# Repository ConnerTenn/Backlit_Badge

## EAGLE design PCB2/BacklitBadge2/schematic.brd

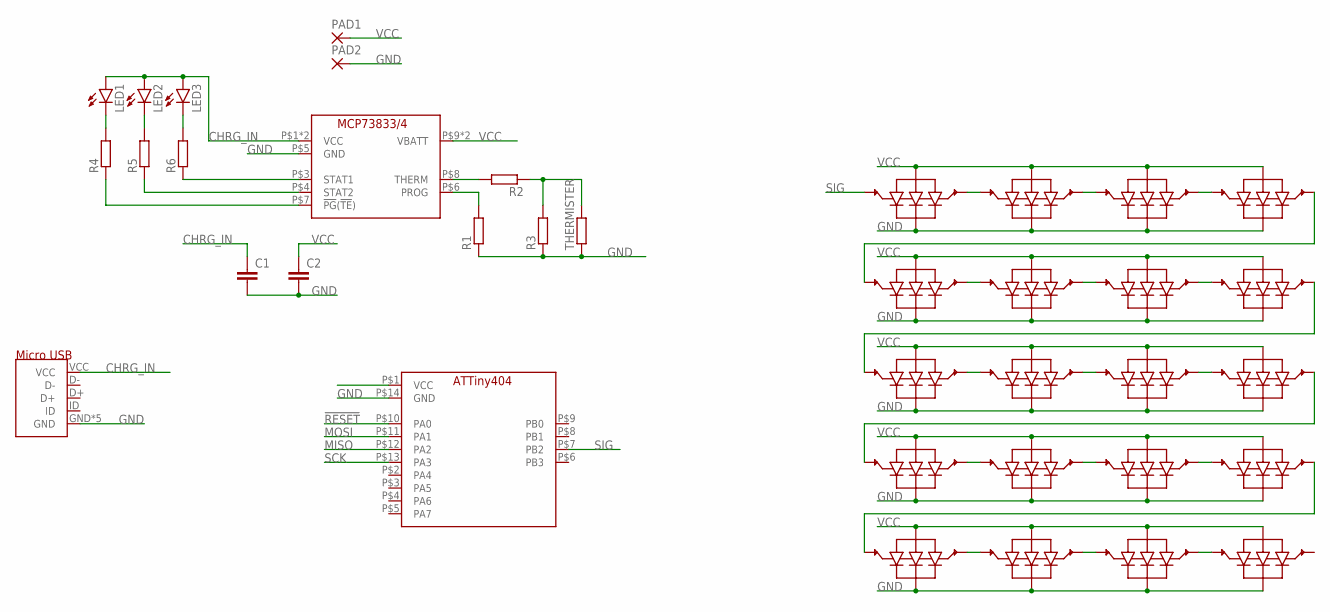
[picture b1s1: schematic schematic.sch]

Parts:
C1, C2: CC1206; C1206
LED1, LED2, LED3: LEDSML1206; SML1206
PAD1, PAD2: 1,6/0,8
R1, R2, R3, R4, R5, R6: RR1206; R1206
THERMISTER: RR1206; R1206
U$1: ATTINY404; 14-SOIC
U$2: MCP73833/4; 10-MSOP
U$3, U$4, U$5, U$6, U$7, U$8, U$9, U$10, U$11, U$12, U$13, U$14, U$15, U$16, U$17, U$18, U$19, U$20, U$21, U$22: WS2812B; 5050-THRU
U$23: MICROUSB

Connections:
!RESET: U$1.P$10 (PA0)
CHRG_IN: C1.1, LED1.A, LED2.A, LED3.A, U$2.P$1 (VCC), U$2.P$2 (VCC), U$23.VCC
GND: C1.2, C2.2, PAD2.1, R1.1, R3.1, THERMISTER.1, U$1.P$14 (GND), U$2.P$5 (GND), U$3.P$3 (GND), U$4.P$3 (GND), U$5.P$3 (GND), U$6.P$3 (GND), U$7.P$3 (GND), U$8.P$3 (GND), U$9.P$3 (GND), U$10.P$3 (GND), U$11.P$3 (GND), U$12.P$3 (GND), U$13.P$3 (GND), U$14.P$3 (GND), U$15.P$3 (GND), U$16.P$3 (GND), U$17.P$3 (GND), U$18.P$3 (GND), U$19.P$3 (GND), U$20.P$3 (GND), U$21.P$3 (GND), U$22.P$3 (GND), U$23.GND, U$23.GND2 (GND), U$23.GND3 (GND), U$23.GND4 (GND), U$23.GND5 (GND)
MISO: U$1.P$12 (PA2)
MOSI: U$1.P$11 (PA1)
unnamed: U$3.P$2 (DOUT), U$4.P$4 (DIN)
unnamed: U$7.P$2 (DOUT), U$8.P$4 (DIN)
unnamed: R1.2, U$2.P$6 (PROG)
unnamed: R2.2, U$2.P$8 (THERM)
unnamed: R2.1, R3.2, THERMISTER.2
unnamed: LED1.C, R4.2
unnamed: LED2.C, R5.2
unnamed: R6.1, U$2.P$3 (STAT1)
unnamed: LED3.C, R6.2
unnamed: U$13.P$2 (DOUT), U$19.P$4 (DIN)
unnamed: U$5.P$2 (DOUT), U$6.P$4 (DIN)
unnamed: U$9.P$2 (DOUT), U$14.P$4 (DIN)
unnamed: U$17.P$2 (DOUT), U$18.P$4 (DIN)
unnamed: R5.1, U$2.P$4 (STAT2)
unnamed: U$10.P$2 (DOUT), U$11.P$4 (DIN)
unnamed: U$11.P$2 (DOUT), U$12.P$4 (DIN)
unnamed: U$12.P$2 (DOUT), U$13.P$4 (DIN)
unnamed: U$4.P$2 (DOUT), U$5.P$4 (DIN)
unnamed: U$8.P$2 (DOUT), U$9.P$4 (DIN)
unnamed: U$16.P$2 (DOUT), U$17.P$4 (DIN)
unnamed: U$21.P$2 (DOUT), U$22.P$4 (DIN)
unnamed: U$20.P$2 (DOUT), U$21.P$4 (DIN)
unnamed: U$15.P$2 (DOUT), U$16.P$4 (DIN)
unnamed: U$18.P$2 (DOUT), U$20.P$4 (DIN)
unnamed: U$14.P$2 (DOUT), U$15.P$4 (DIN)
unnamed: U$6.P$2 (DOUT), U$7.P$4 (DIN)
unnamed: U$3.P$4 (DIN), U$19.P$2 (DOUT)
unnamed: R4.1, U$2.P$7 (!PG!(!TE!))
SCK: U$1.P$13 (PA3)
SIG: U$1.P$7 (PB2), U$10.P$4 (DIN)
VCC: C2.1, PAD1.1, U$2.P$9 (VBATT), U$2.P$10 (VBATT), U$3.P$1 (VCC), U$4.P$1 (VCC), U$5.P$1 (VCC), U$6.P$1 (VCC), U$7.P$1 (VCC), U$8.P$1 (VCC), U$9.P$1 (VCC), U$10.P$1 (VCC), U$11.P$1 (VCC), U$12.P$1 (VCC), U$13.P$1 (VCC), U$14.P$1 (VCC), U$15.P$1 (VCC), U$16.P$1 (VCC), U$17.P$1 (VCC), U$18.P$1 (VCC), U$19.P$1 (VCC), U$20.P$1 (VCC), U$21.P$1 (VCC), U$22.P$1 (VCC)

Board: 2 copper layers, 37 parts (20 on the bottom side), 32 nets, no tracks yet.

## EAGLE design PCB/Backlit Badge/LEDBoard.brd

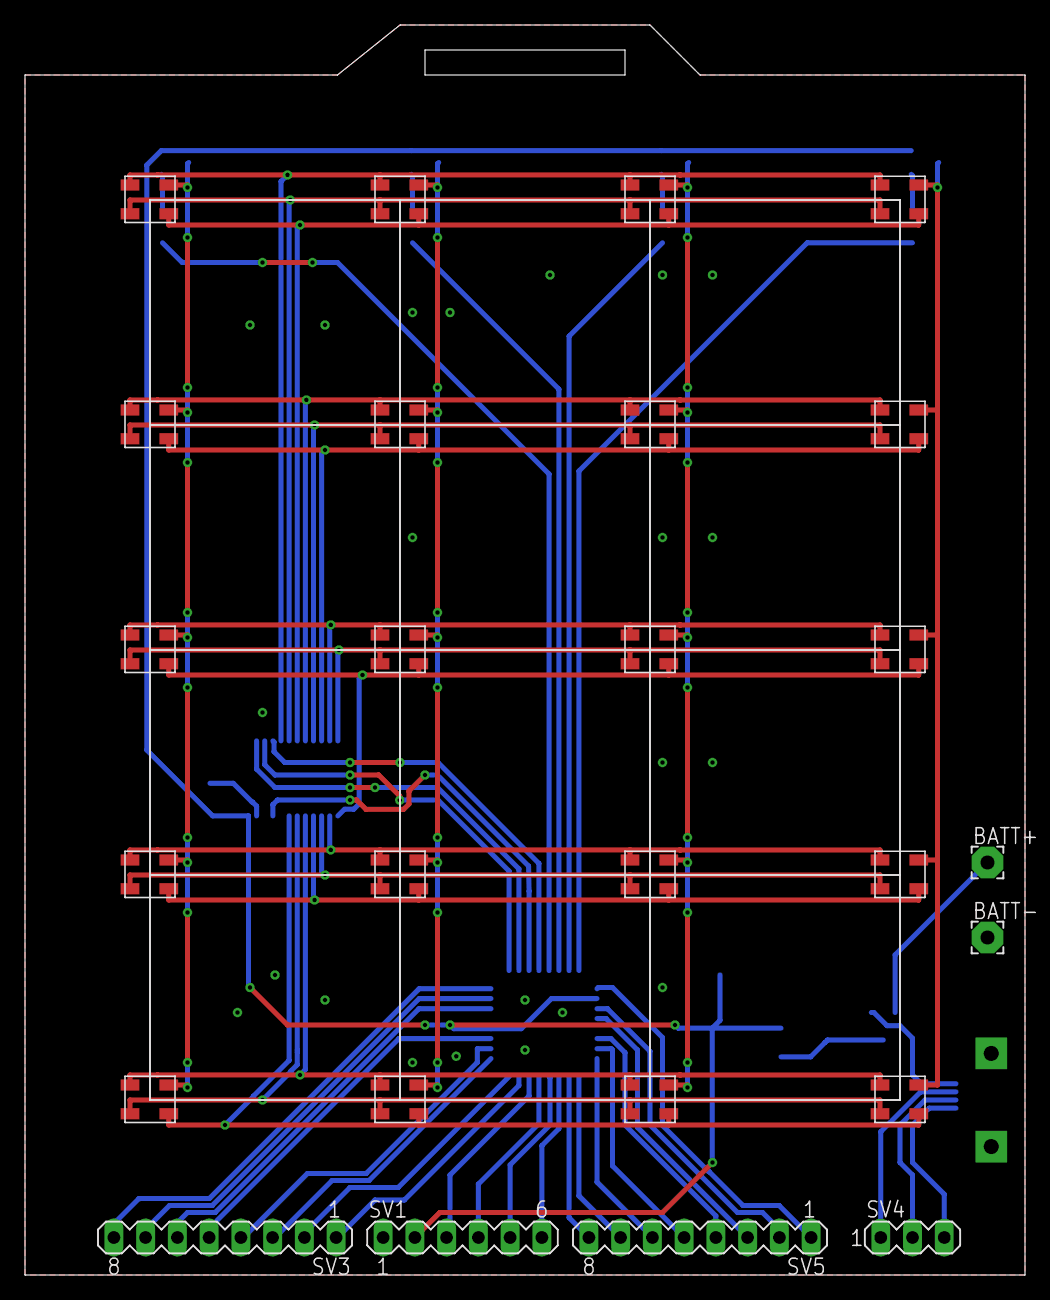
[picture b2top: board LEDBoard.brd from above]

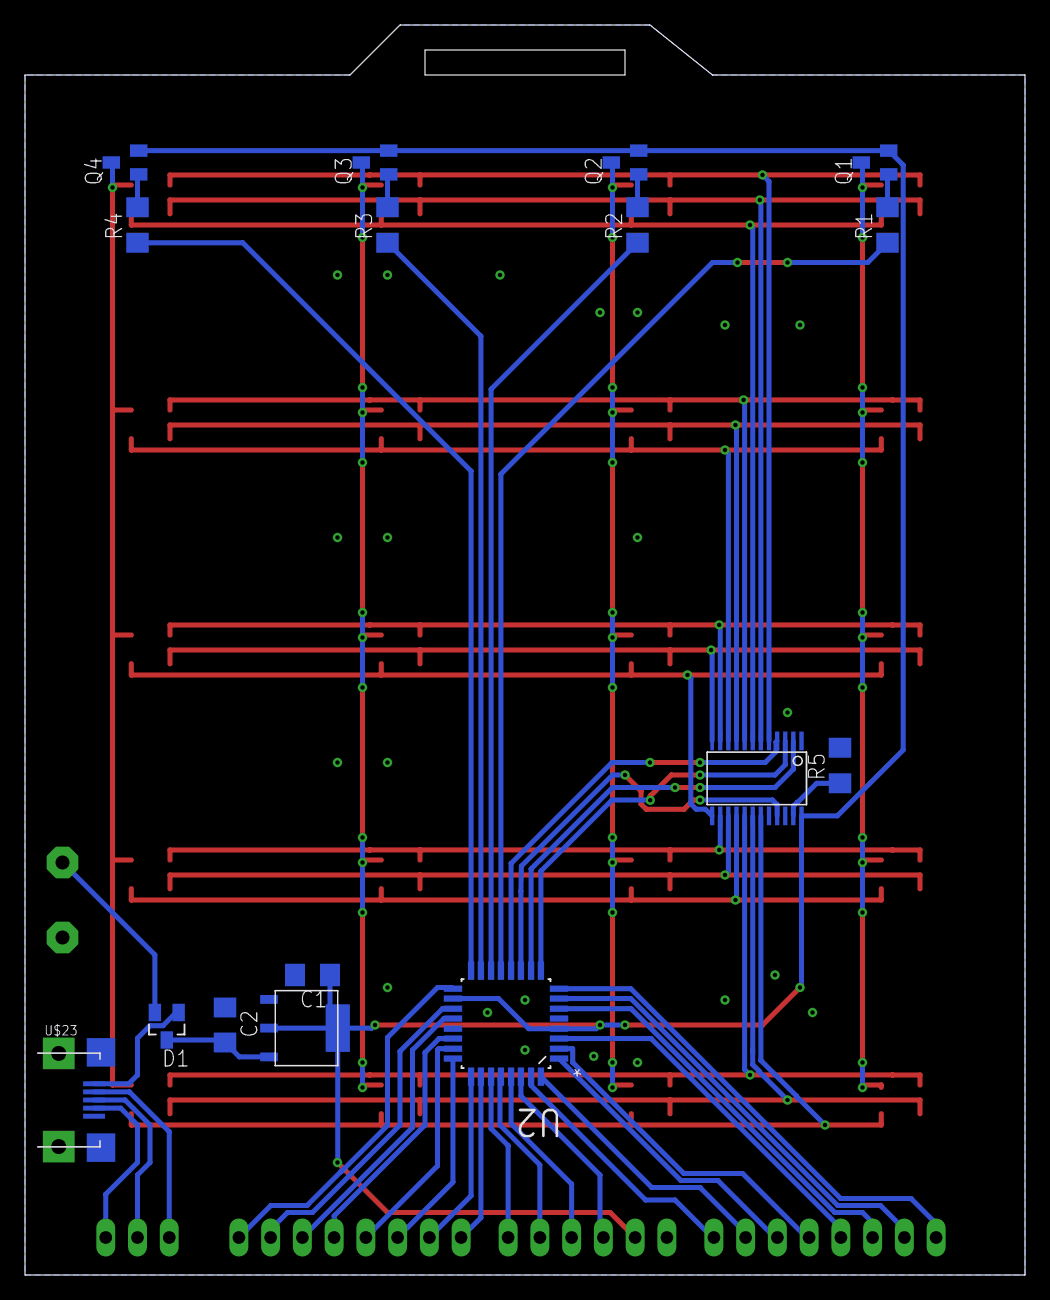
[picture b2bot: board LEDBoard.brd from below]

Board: 2 copper layers, 80.0 x 100.0 mm, 42 parts (16 on the bottom side), 60 nets.

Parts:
BATT+: 2,54/1,1
BATT-: 2,54/1,1
C1, C2: C1206
D1: SOT23
Q1, Q2, Q3, Q4: MMBTA56-SOT23; SOT23
R1, R2, R3, R4, R5: R1206
SV1: MA06-1
SV3, SV5: MA08-1
SV4: MA03-1
U2: ATTINY828R-AU; QFP80P900X900X120-32N
U$1: IS31FL3726; TSSOP-24
U$2: AP2114H; SOT233
U$3, U$4, U$5, U$6, U$7, U$8, U$9, U$10, U$11, U$12, U$13, U$14, U$15, U$16, U$17, U$18, U$19, U$20, U$21, U$22: 3528LED; 3528
U$23: MICRO-USB

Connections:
!EN: U2.11, U$1.21
!LA: U2.12, U$1.4
!RESET: SV1.4, U2.29
CLK: U2.9, U$1.3
COL0: R1.1, U2.13
COL1: R2.1, U2.14
COL2: R3.1, U2.15
COL3: R4.1, U2.16
GND: BATT-.1, C1.2, C2.1, R5.2, SV1.1, U2.5, U2.21, U$1.1, U$2.P$1, U$23.5, U$23.GND1, U$23.GND2
MISO: SV1.5, U2.28
MOSI: SV1.6, U2.27
unnamed: SV3.1, U2.31
unnamed: SV3.2, U2.32
unnamed: U$1.5, U$7.P$1, U$8.P$1, U$9.P$1, U$10.P$1
unnamed: U$1.6, U$7.P$3, U$8.P$3, U$9.P$3, U$10.P$3
unnamed: U$1.7, U$7.P$4, U$8.P$4, U$9.P$4, U$10.P$4
unnamed: U$1.8, U$3.P$1, U$4.P$1, U$5.P$1, U$6.P$1
unnamed: U$1.9, U$3.P$3, U$4.P$3, U$5.P$3, U$6.P$3
unnamed: U$1.10, U$3.P$4, U$4.P$4, U$5.P$4, U$6.P$4
unnamed: U$1.11, U$11.P$1, U$12.P$1, U$13.P$1, U$14.P$1
unnamed: U$1.12, U$11.P$3, U$12.P$3, U$13.P$3, U$14.P$3
unnamed: U$1.13, U$11.P$4, U$12.P$4, U$13.P$4, U$14.P$4
unnamed: U$1.14, U$15.P$1, U$16.P$1, U$17.P$1, U$18.P$1
unnamed: U$1.15, U$15.P$3, U$16.P$3, U$17.P$3, U$18.P$3
unnamed: U$1.16, U$15.P$4, U$16.P$4, U$17.P$4, U$18.P$4
unnamed: U$1.17, U$19.P$1, U$20.P$1, U$21.P$1, U$22.P$1
unnamed: U$1.18, U$19.P$3, U$20.P$3, U$21.P$3, U$22.P$3
unnamed: U$1.19, U$19.P$4, U$20.P$4, U$21.P$4, U$22.P$4
unnamed: Q1.3, U$3.P$2, U$7.P$2, U$11.P$2, U$15.P$2, U$22.P$2
unnamed: Q2.3, U$4.P$2, U$8.P$2, U$12.P$2, U$16.P$2, U$21.P$2
unnamed: Q3.3, U$5.P$2, U$9.P$2, U$13.P$2, U$17.P$2, U$20.P$2
unnamed: Q4.3, U$6.P$2, U$10.P$2, U$14.P$2, U$18.P$2, U$19.P$2
unnamed: Q1.1, R1.2
unnamed: Q2.1, R2.2
unnamed: Q3.1, R3.2
unnamed: Q4.1, R4.2
unnamed: R5.1, U$1.23
unnamed: SV3.3, U2.1
unnamed: SV3.4, U2.2
unnamed: SV3.5, U2.3
unnamed: SV3.6, U2.6
unnamed: SV3.7, U2.7
unnamed: SV3.8, U2.8
unnamed: SV5.1, U2.17
unnamed: SV5.2, U2.19
unnamed: SV5.3, U2.20
unnamed: SV5.4, U2.22
unnamed: SV5.5, U2.23
unnamed: SV5.6, U2.24
unnamed: SV5.7, U2.25
unnamed: SV5.8, U2.26
unnamed: SV4.1, U$23.2
unnamed: D1.1, U$23.1
unnamed: SV4.2, U$23.3
unnamed: BATT+.1, D1.2
unnamed: SV4.3, U$23.4
SCK: SV1.3, U2.30
SERIAL: U2.10, U$1.2
VCC: C1.1, Q1.2, Q2.2, Q3.2, Q4.2, SV1.2, U2.4, U2.18, U$1.24, U$2.P$2, U$2.P$4
VPP: C2.2, D1.3, U$2.P$3

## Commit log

2018-05-01 Added .gitignore
2018-05-01 Migrated files to here from Personal Repository
2019-04-08 Began designing Version 2
2019-04-08 Updates to the schematic
2019-04-17 More updates
